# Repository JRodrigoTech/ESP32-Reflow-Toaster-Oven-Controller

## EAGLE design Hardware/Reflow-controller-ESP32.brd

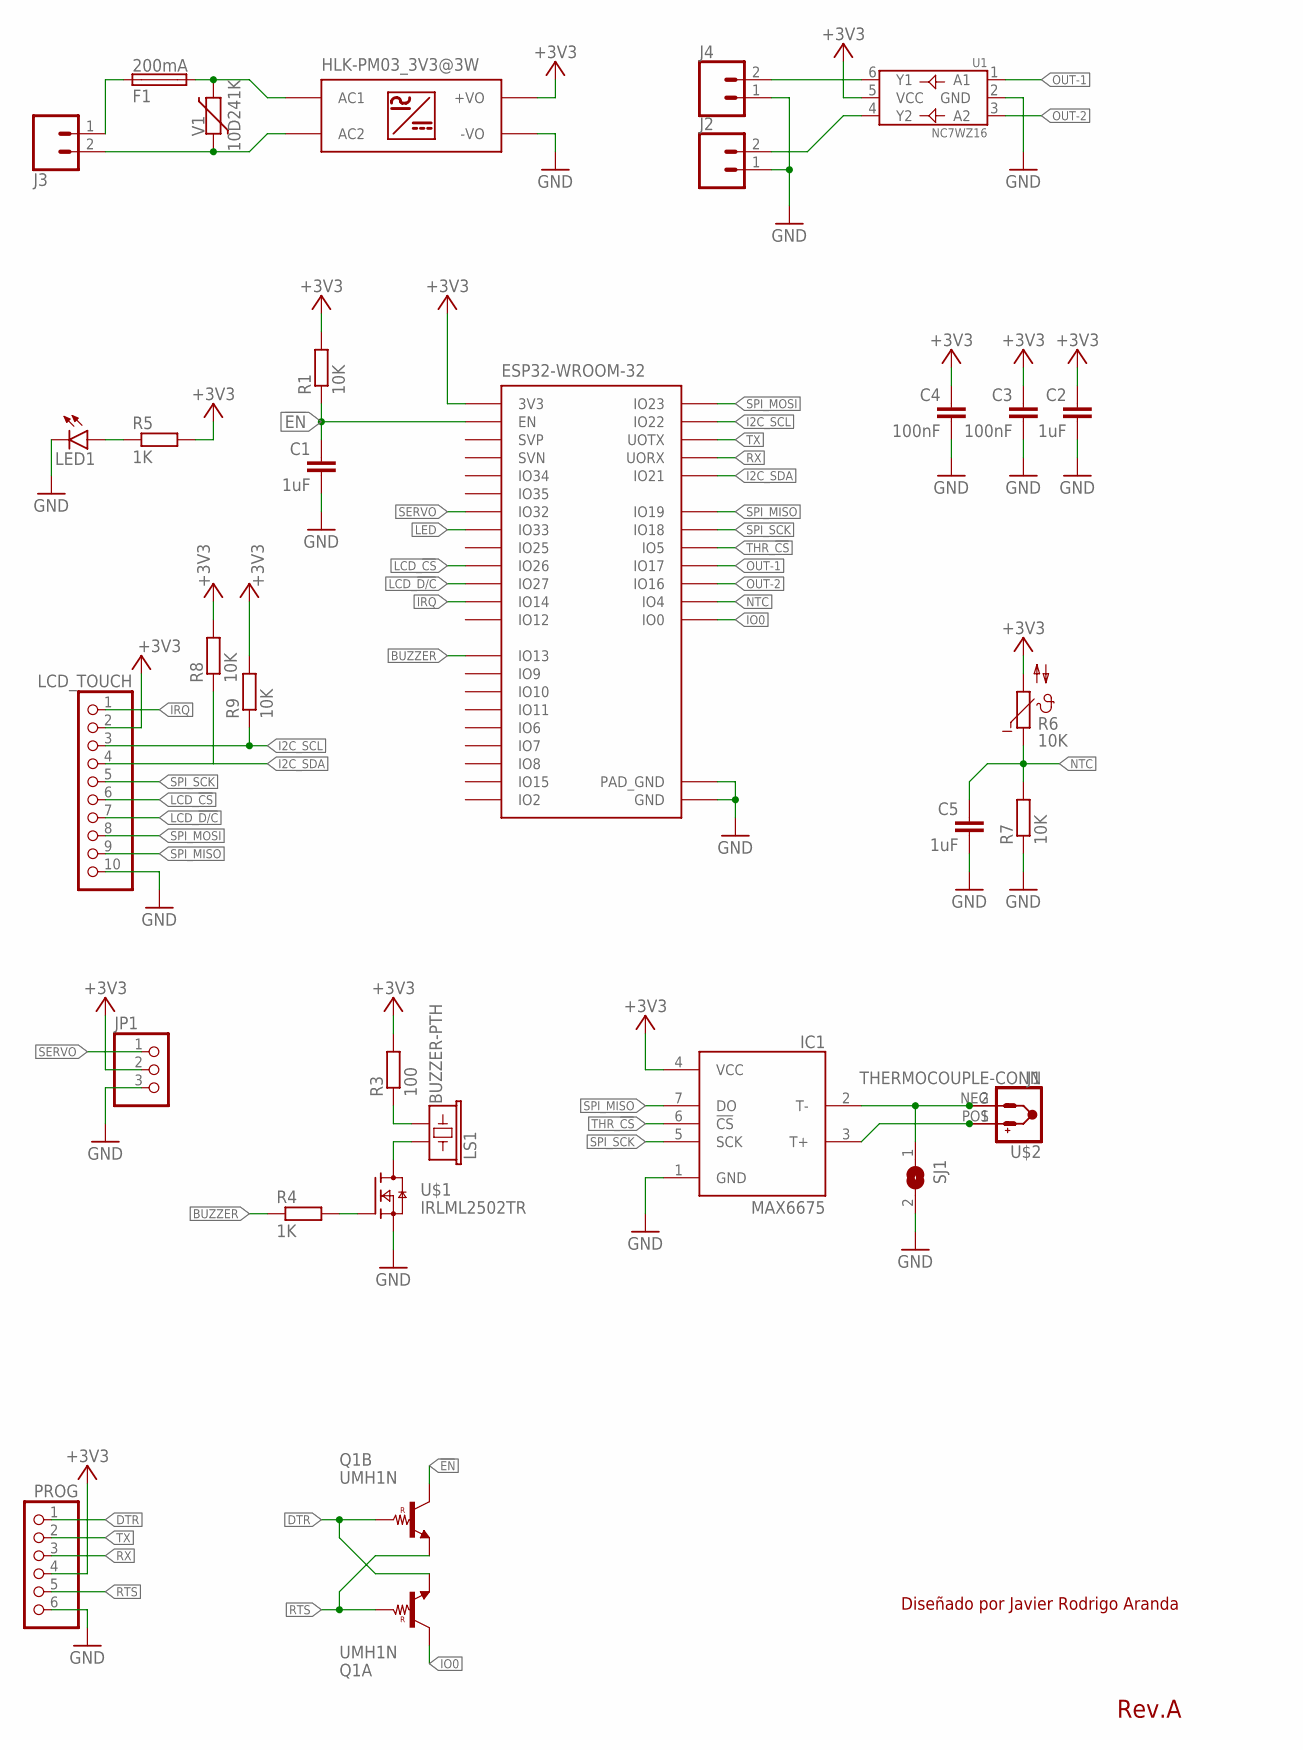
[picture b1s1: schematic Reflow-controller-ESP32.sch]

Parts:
C1, C2, C5: 1uF; C0805
C3, C4: 100nF; C0805
ESP32-WROOM-32: ESP32; ESP32-WROOM-32
F1: 200mA; SH22,5
HLK-PM03_3V3@3W: HLK-PM0X
IC1: MAX6675; SO08
J1, J2, J3, J4: HEADER_01X025MM-BIG; SCREWTERMINAL-5MM-BIG-BLOCK
JP1: PINHD-1X3; 1X03
LCD_TOUCH: PINHD-1X10; 1X10
LED1: LEDSML1206; SML1206
LS1: BUZZER-PTH; BUZZER-12MM
PROG: PINHD-1X6; 1X06
Q1: UMH1N; UMT6
R1, R7, R8, R9: 10K; R0805
R3: 100; R0805
R4, R5: 1K; R0805
R6: 10K; P642
SJ1: SJ
U1: NC7WZ16; SC-70-6
U$1: IRLML2502TR; SOT23-3
U$2: THERMOCOUPLE-CONN; THERMOCOUPLE-ONBOARD-CONN
V1: 10D241K; R-7,5

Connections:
!EN: C1.1, ESP32-WROOM-32.3 (EN), Q1.3 (C), R1.1
+3V3: C2.1, C3.1, C4.1, ESP32-WROOM-32.2 (3V3), HLK-PM03_3V3@3W.P$4 (+VO), IC1.4 (VCC), JP1.2, LCD_TOUCH.2, PROG.4, R1.2, R3.2, R5.2, R6.2, R8.2, R9.2, U1.5 (VCC)
AC+: HLK-PM03_3V3@3W.P$2 (AC2), J3.2, V1.1
AC-: F1.2, HLK-PM03_3V3@3W.P$1 (AC1), V1.2
BOUT1: J4.2, U1.6 (Y1)
BOUT2: J2.2, U1.4 (Y2)
BUZZER: ESP32-WROOM-32.16 (IO13), R4.1
DTR: PROG.1, Q1.1 (E), Q1.5 (B)
GND: C1.2, C2.2, C3.2, C4.2, C5.2, ESP32-WROOM-32.1 (GND), ESP32-WROOM-32.15 (GND), ESP32-WROOM-32.38 (GND), ESP32-WROOM-32.GND (PAD_GND), HLK-PM03_3V3@3W.P$3 (-VO), IC1.1 (GND), J2.1, J4.1, JP1.3, LCD_TOUCH.10, LED1.C, PROG.6, R7.1, SJ1.2, U1.2 (GND), U$1.2 (S)
I2C_SCL: ESP32-WROOM-32.36 (IO22), LCD_TOUCH.3, R9.1
I2C_SDA: ESP32-WROOM-32.33 (IO21), LCD_TOUCH.4, R8.1
IO0: ESP32-WROOM-32.25 (IO0), Q1.6 (C)
IRQ: ESP32-WROOM-32.13 (IO14), LCD_TOUCH.1
LCD_!CS: ESP32-WROOM-32.11 (IO26), LCD_TOUCH.6
LCD_!D/C: ESP32-WROOM-32.12 (IO27), LCD_TOUCH.7
LED: ESP32-WROOM-32.9 (IO33)
unnamed: F1.1, J3.1
unnamed: LED1.A, R5.1
unnamed: IC1.3 (T+), J1.1, U$2.POS
unnamed: LS1.- (2), R3.1
unnamed: LS1.+ (1), U$1.3 (D)
unnamed: R4.2, U$1.1 (G)
unnamed: IC1.2 (T-), J1.2, SJ1.1, U$2.NEG
NTC: C5.1, ESP32-WROOM-32.26 (IO4), R6.1, R7.2
OUT-1: ESP32-WROOM-32.28 (IO17), U1.1 (A1)
OUT-2: ESP32-WROOM-32.27 (IO16), U1.3 (A2)
RTS: PROG.5, Q1.2 (B), Q1.4 (E)
RX: ESP32-WROOM-32.34 (UORX), PROG.3
SERVO: ESP32-WROOM-32.8 (IO32), JP1.1
SPI_MISO: ESP32-WROOM-32.31 (IO19), IC1.7 (DO), LCD_TOUCH.9
SPI_MOSI: ESP32-WROOM-32.37 (IO23), LCD_TOUCH.8
SPI_SCK: ESP32-WROOM-32.30 (IO18), IC1.5 (SCK), LCD_TOUCH.5
THR_!CS: ESP32-WROOM-32.29 (IO5), IC1.6 (!CS)
TX: ESP32-WROOM-32.35 (UOTX), PROG.2

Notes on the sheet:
Rev.A
Diseñado por Javier Rodrigo Aranda

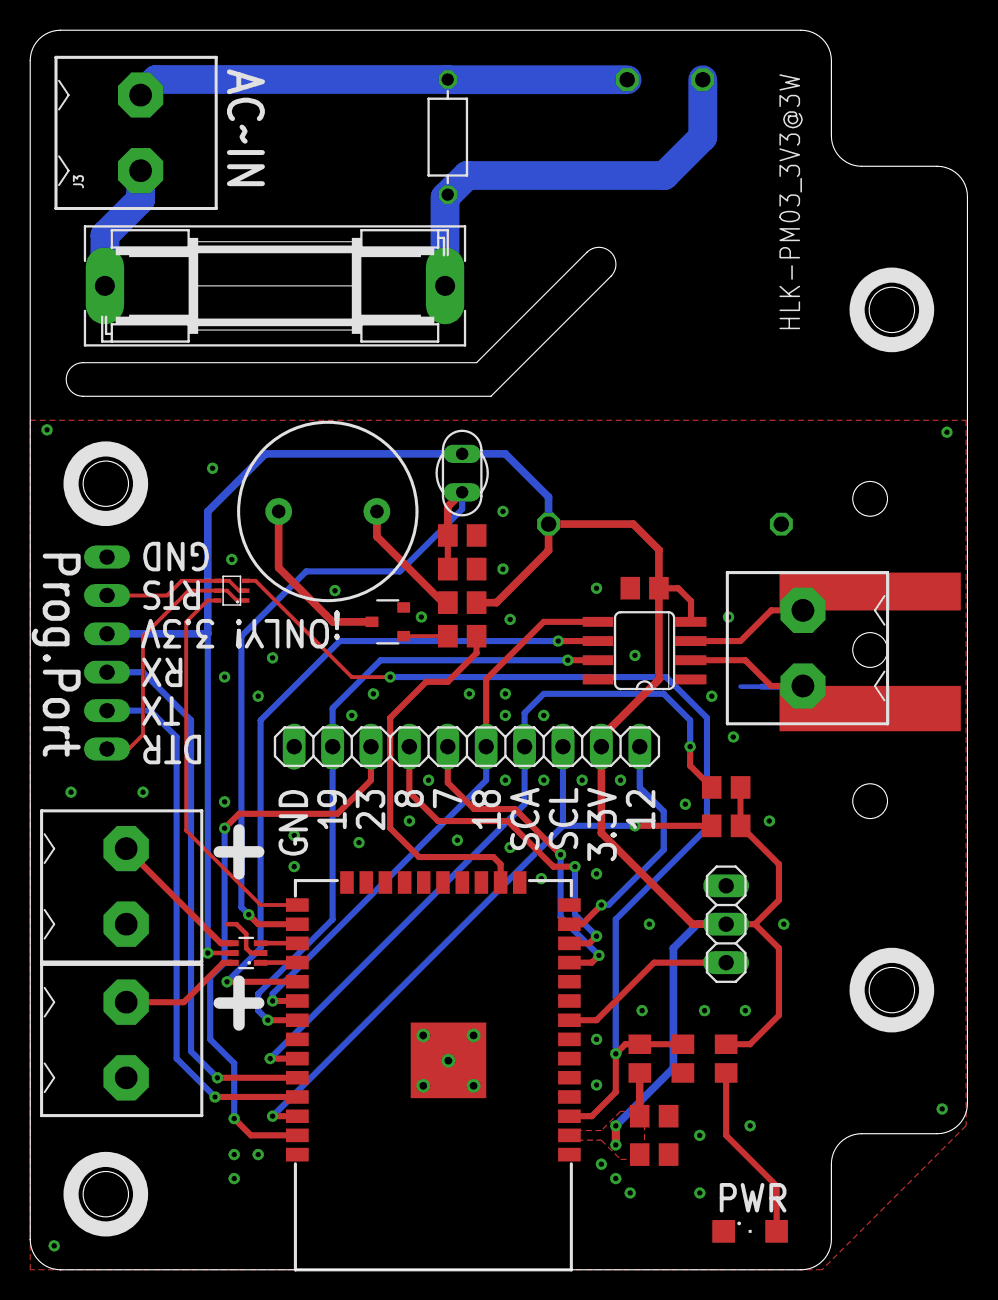
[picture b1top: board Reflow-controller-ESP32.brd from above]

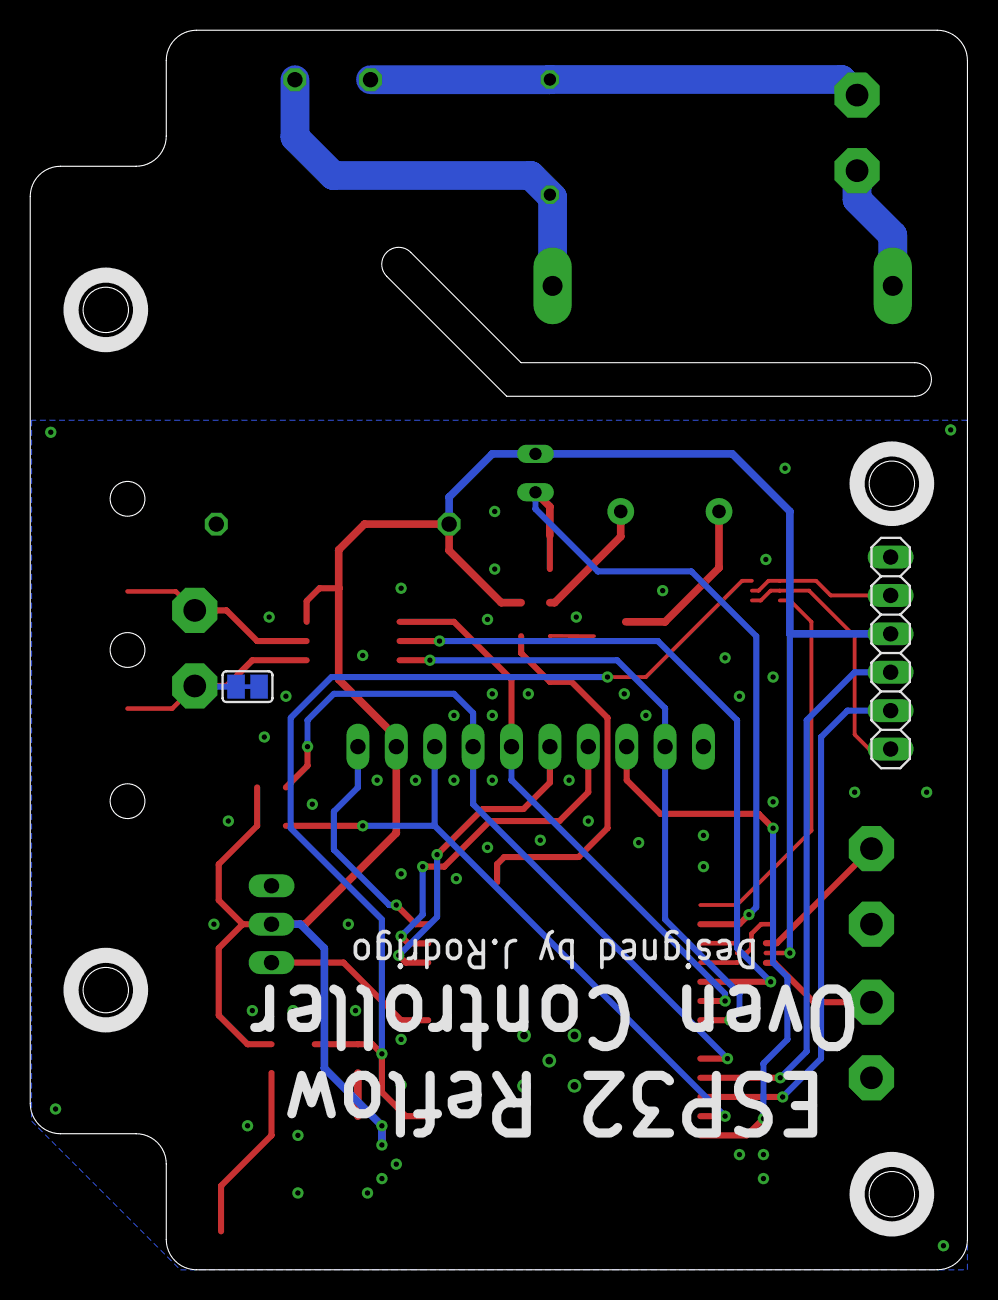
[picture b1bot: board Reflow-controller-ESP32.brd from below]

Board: 2 copper layers, 62.0 x 82.0 mm, 32 parts (2 on the bottom side), 33 nets.

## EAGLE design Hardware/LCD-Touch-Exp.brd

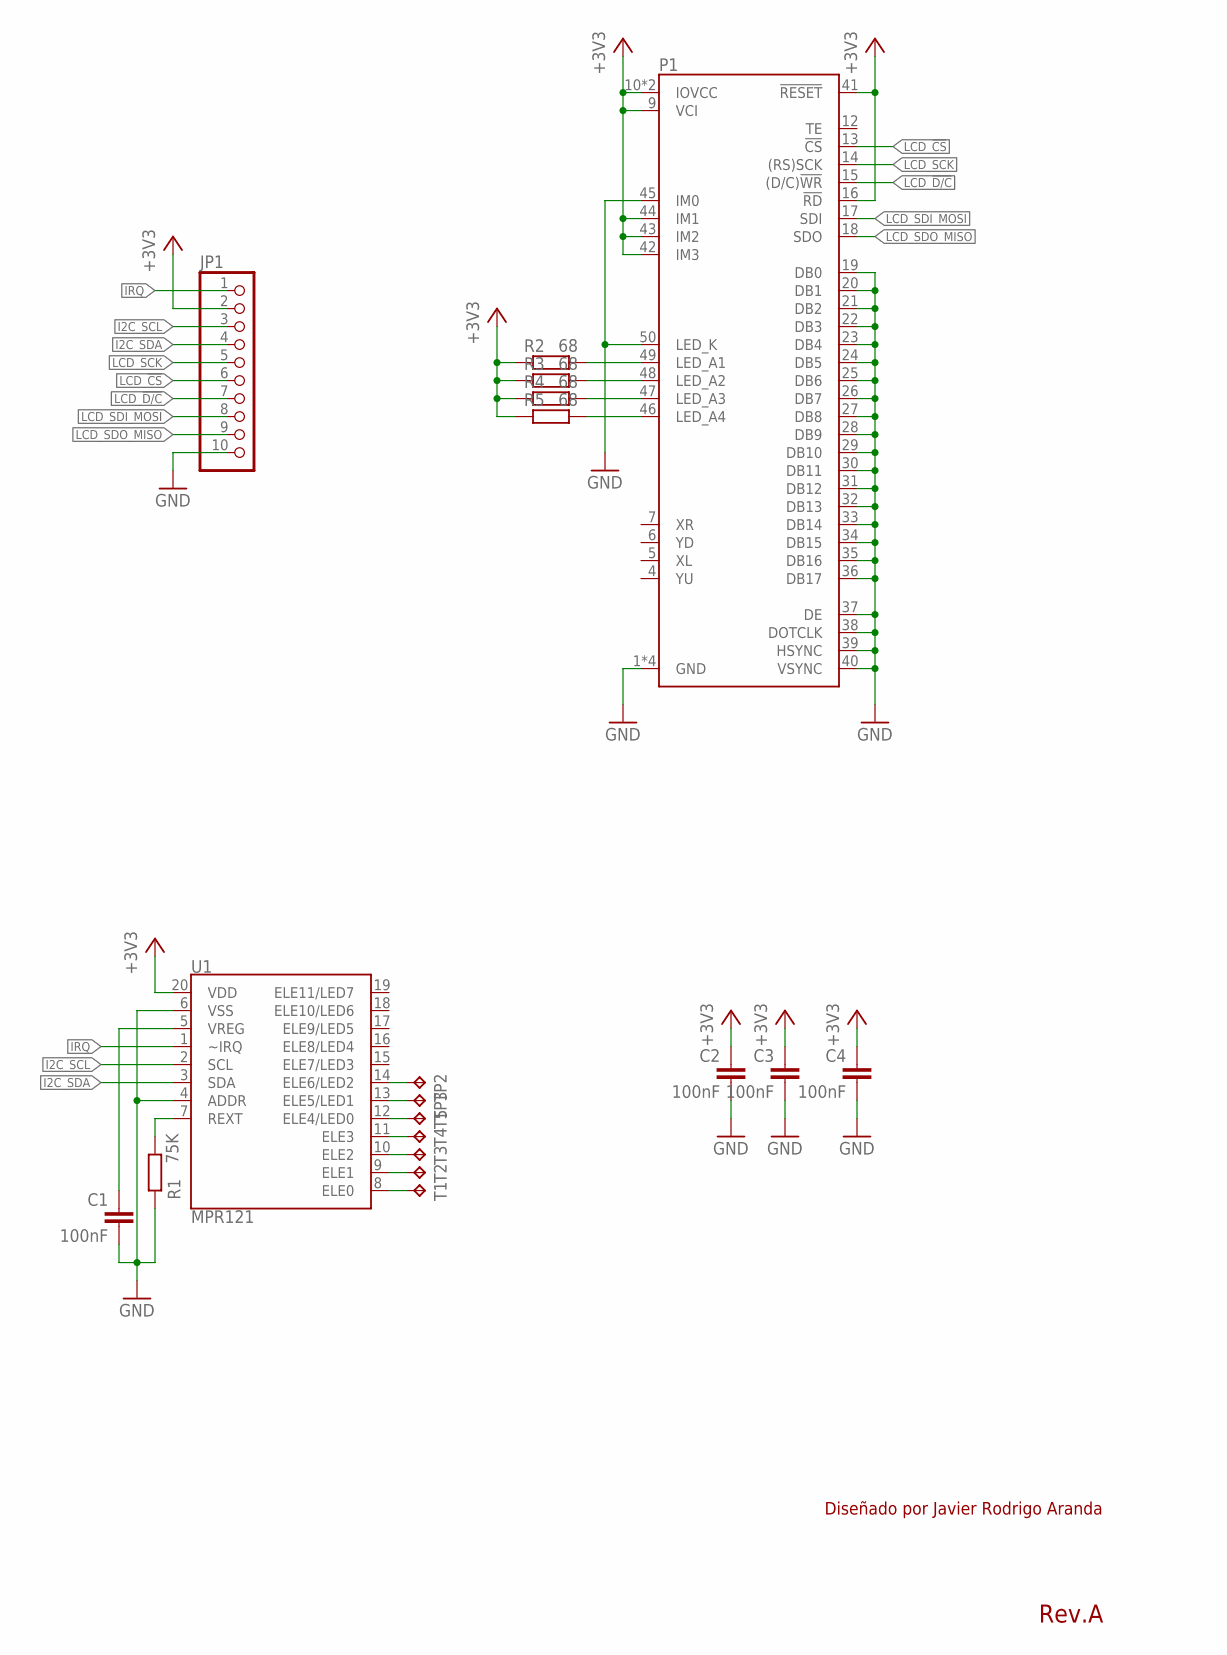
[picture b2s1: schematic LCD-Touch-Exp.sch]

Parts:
C1, C2, C3, C4: 100nF; C0805
JP1: HEADER-1X10SMT; 1X10_SMT
P1: LCD_ILI9341180º; FPC-50P-0.5MM
R1: 75K; R0805
R2, R3, R4, R5: 68; R0603
T1, T2, T3, T4, T5: TPB1,27; B1,27
TP2, TP3: TPB1,27; B1,27
U1: MPR121; QFN-20

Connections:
+3V3: C2.1, C3.1, C4.1, JP1.2, P1.9 (VCI), P1.10 (IOVCC), P1.11 (IOVCC), P1.16 (!RD), P1.41 (!RESET), P1.42 (IM3), P1.43 (IM2), P1.44 (IM1), R2.2, R3.2, R4.2, R5.2, U1.20 (VDD)
GND: C1.2, C2.2, C3.2, C4.2, JP1.10, P1.1 (GND), P1.2 (GND), P1.3 (GND), P1.8 (GND), P1.19 (DB0), P1.20 (DB1), P1.21 (DB2), P1.22 (DB3), P1.23 (DB4), P1.24 (DB5), P1.25 (DB6), P1.26 (DB7), P1.27 (DB8), P1.28 (DB9), P1.29 (DB10), P1.30 (DB11), P1.31 (DB12), P1.32 (DB13), P1.33 (DB14), P1.34 (DB15), P1.35 (DB16), P1.36 (DB17), P1.37 (DE), P1.38 (DOTCLK), P1.39 (HSYNC), P1.40 (VSYNC), P1.45 (IM0), P1.50 (LED_K), R1.1, U1.4 (ADDR), U1.6 (VSS)
I2C_SCL: JP1.3, U1.2 (SCL)
I2C_SDA: JP1.4, U1.3 (SDA)
IRQ: JP1.1, U1.1 (~IRQ)
LCD_!CS: JP1.6, P1.13 (!CS)
LCD_!D/C: JP1.7, P1.15 ((D/C)!WR!)
LCD_SCK: JP1.5, P1.14 ((RS)SCK)
LCD_SDI_MOSI: JP1.8, P1.17 (SDI)
LCD_SDO_MISO: JP1.9, P1.18 (SDO)
unnamed: R1.2, U1.7 (REXT)
unnamed: T1.TP, U1.8 (ELE0)
unnamed: T2.TP, U1.9 (ELE1)
unnamed: T3.TP, U1.10 (ELE2)
unnamed: T4.TP, U1.11 (ELE3)
unnamed: T5.TP, U1.12 (ELE4/LED0)
unnamed: TP3.TP, U1.13 (ELE5/LED1)
unnamed: TP2.TP, U1.14 (ELE6/LED2)
unnamed: P1.49 (LED_A1), R2.1
unnamed: P1.48 (LED_A2), R3.1
unnamed: P1.47 (LED_A3), R4.1
unnamed: P1.46 (LED_A4), R5.1
unnamed: C1.1, U1.5 (VREG)

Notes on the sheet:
Rev.A
Diseñado por Javier Rodrigo Aranda

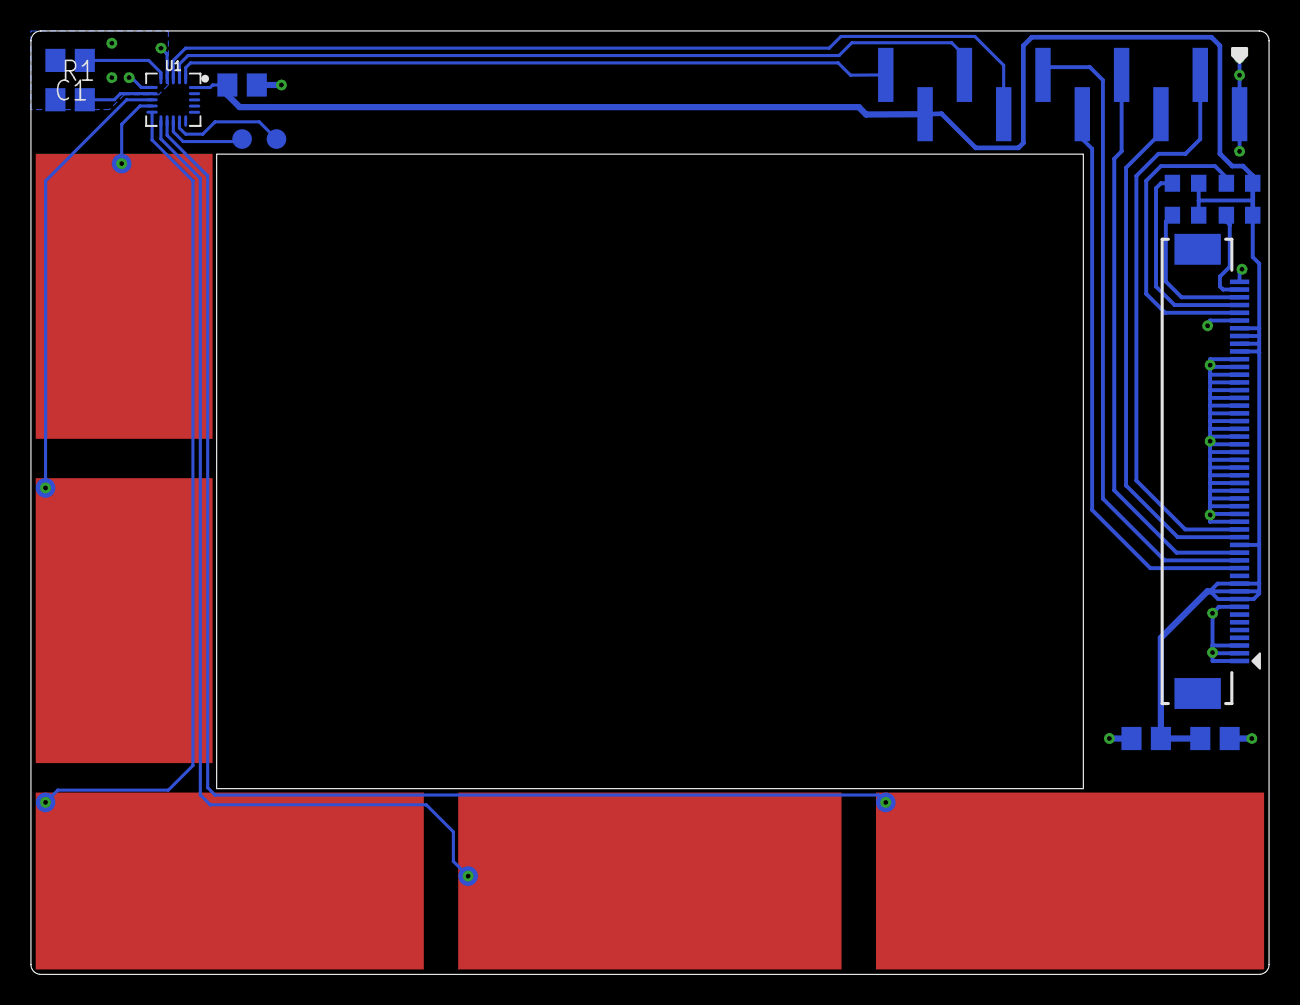
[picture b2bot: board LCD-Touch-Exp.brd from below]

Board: 2 copper layers, 80.0 x 61.0 mm, 19 parts (19 on the bottom side), 23 nets.

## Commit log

2019-02-17 Initial commit
    First basic test version of the code with wifi client and AP modes, thermocouple reading and a basic web.
2019-02-17 Added the acquisition of parameters via URL
    And fixed the problem with the captive portal
2019-02-18 Configuration page with saved in EEPROM
2019-03-31 Some more improvements
    - Fix EEPROM save pagination
    - Dual-Core functionality
    - Improved web interface
2019-03-31 Code commented and polited
2019-04-01 Improved canvas plot
    - Live reflow plot temperature
    - Simplified some functions of the code
    - Print current local IP
2019-04-02 First profile temperature controller
    - Implemented a proportional ramp profile controller
    - "Variables.h" file created for variables and definitions
2019-04-02 Renamed to EEPROM.h
2019-04-02 Minimal Fix
    - EEPROM_FUNCTIONS.h changed to EEPROM.h
    - The code has been cleaned up
2019-04-07 html.h minor updates
    - 00,0 ºC to nan ºC
    - New version 0.0.1b
2019-04-07 LCD & Touch
    - Implemented the ILI9341 LCD screen
    - Implemented the MPR121 touch control input
    Note: You can disable the LCD screen and the touch input commenting the //#define LCD_TOUCH
2019-04-27 touch.h merged into LCD.h
2019-04-27 Source files needed
    Backup folder to ensure its future compilations.
2019-05-02 Added first hardware revision
2019-05-02 Source code moved to "Software" folder

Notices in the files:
parts and their libraries:
SparkFun-Sensors: Licensing: Creative Commons ShareAlike 4.0 International - https://creativecommons.org/licenses/by-sa/4.0
jrodrigo: Creative Commons - Attribution and Share Alike 4.0 International - https://creativecommons.org/licenses/by-sa/4.0
